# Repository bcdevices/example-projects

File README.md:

# Example Projects

A collection of KiCad hardware design projects, well mostly KiCad.
Confiential files should not be placed here!

## Structure

Each project lives in its own folder:

```
example-projects/
├── board-name-1/
│   ├── board-name-1.kicad_pro
│   ├── board-name-1.kicad_pcb
│   ├── board-name-1.kicad_sch
│   └── bom.csv
└── board-name-2/
    └── ...
```

## Files

| Extension | Description |
|---|---|
| `.kicad_pro` | KiCad project file |
| `.kicad_pcb` | PCB layout |
| `.kicad_sch` | Schematic |
| `.csv` | Bill of materials |

## Requirements

- [KiCad](https://www.kicad.org) 7.0 or later

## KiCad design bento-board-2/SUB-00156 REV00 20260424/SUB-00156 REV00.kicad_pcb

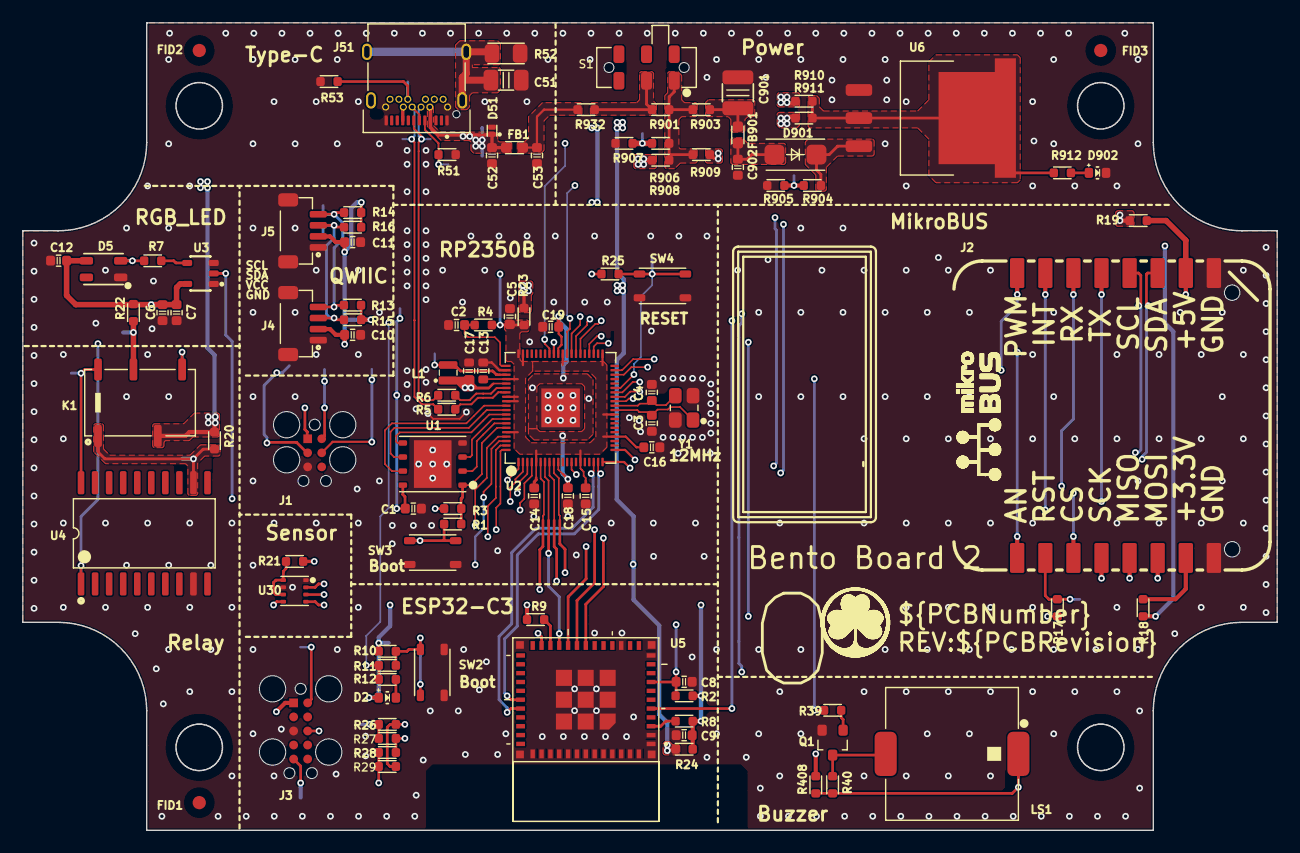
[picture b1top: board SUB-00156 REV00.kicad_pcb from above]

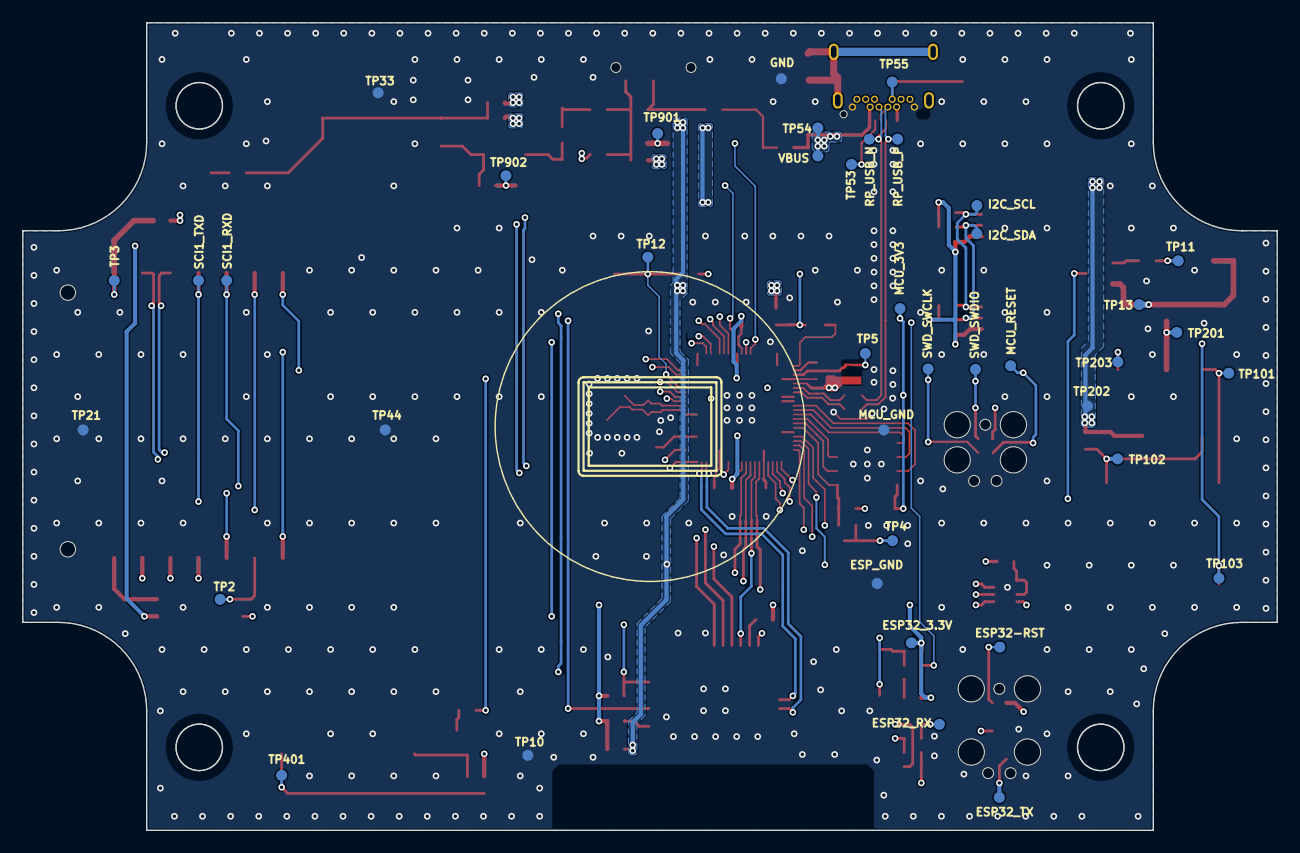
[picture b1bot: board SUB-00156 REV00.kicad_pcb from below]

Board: 4 copper layers, 113.4 x 73.0 mm, 153 parts (42 on the bottom side), 85 nets.

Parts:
BCD-Logo: BCD-Logo; LOGO_BCD_Product
Board ID label: 8*12mm; Laebl_12*8mm
C1, C7, C10, C11, C12, C14, C15, C16, C18, C19, C902: 0.1μF; CC0603-N
C2, C5, C9: 4.7μF; CC0603-N
C3, C4: 12pF; CC0603-N
C6, C8: 1μF; CC0603-N
C13, C17: 0.1μF; CC0603(1608)-N
C51: 100pF; CC1206-N
C52, C53: 100pF; CC0603-N
C901: 10μF; CC1210-N
D2, D902: LTST-C191KGKT; LED0603N-Green
D5: LTST-E683CEGBW; LTST-E683CEGBW-L
D51: SZESD7241N2T5G; 2-X2DFN (1x0.6)
D901: SK34A-LTP; SMA
ESP32-RST, ESP32_3.3V, ESP32_RX, ESP32_TX: TP-SM-39MILC
ESP_GND: TP-SM-39MILC
FB1, FB901: 26 Ohms@100 MHz; FB0603-N
FID1, FID2, FID3: Mark
GND: TP-SM-39MILC
I2C_SCL, I2C_SDA: TP-SM-39MILC
J1: TC2030-MCP-NL; TC2030-IDC
J2: MIKROE-4319
J3: TC2050-IDC
J4, J5: 16766
J51: 10159872-00011LF
K1: 1462042-8
L1: 3.3µH; IND-201610_SMD-2N
LS1: PKLCS1212E4001-R1
MCU_3V3: TP-SM-39MILC
MCU_GND: TP-SM-39MILC
MCU_RESET: TP-SM-39MILC
MH1, MH2, MH3, MH4: MountingHole; MH_.165NPT
OSHWA-Logo: OSHWA-Logo
PCB: CMP-000451 REV:00; PCB Part Number
PLT Tested label: 24*12mm; Laebl_24*12mm
Q1: MMBT3904-TP; SOT23
R1: 2K; RC0603-N
R2, R9, R10, R12, R13, R14, R15, R16: 10K; RC0603-N
R3, R25, R904: 100K; RC0603-N
R4, R5, R6: 27R; RC0603-N
R7: 1R; RC0603-N
R8, R11, R17, R18, R19, R20, R21, R22, R23, R24, R26, R27, R28, R29, R408, R901, R903, R908, R909, R910, R911, R932: 0R; RC0603-N
R39: 4.7K; RC0603-N
R40: 470R; RC0603-N
R51, R53: 5.1K; RC0603-N
R52: 267K; RC1206-N
R905: 150K; RC0603-N
R906: 470K; RC0603-N
R907: 68K; RC0603-N
R912: 1K; RC0603-N
RP_USB_N: TP-SM-39MILC
RP_USB_P: TP-SM-39MILC
S1: JS202011JAQN
SCI1_RXD, SCI1_TXD: TP-SM-39MILC
SW2, SW3, SW4: PTS810SJG250SMTR LFS
SWD_SWCLK: TP-SM-39MILC
SWD_SWDIO: TP-SM-39MILC
TP2, TP3, TP4, TP5, TP10, TP11, TP12, TP13, TP21, TP33, TP44, TP53, TP54, TP55, TP101, TP102, TP103, TP201, TP202, TP203, TP401, TP901, TP902: TP-SM-39MILC
U1: W25Q128JVPIQ; WSON127P6X5-8NP
U2: RP2350B; QFN040P10X10-80NPV
U3: SN74LVC1G125DBVR; SOT23-5
U4: ULN2803CDWR; SOIC127P10.3X2.65-20N
U5: ESP32-C3-MINI-1-N4
U6: LM1086ISX-3.3/NOPB; TO-263
U30: BME280; LGA065P2.5X2.5-8N
VBUS: TP-SM-39MILC
Y1: 12 MHz; OSC3.2X2.5-4N

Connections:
+3.3V: R21.1, R23.1, R24.1, R408.1, R911.2
+5V: K1.3, R20.2, R908.2, TP202.1
ADC0: R904.2, R905.1, TP902.1, U2.49
ADC1: J2.1, U2.52
ADC2: R906.2, R907.1, TP901.1, U2.53
AUDIO_EN: Q1.1, R39.2
AVDD: C2.1, R4.1, U2.61
BOOT: R10.1, R11.1, SW2.3, SW2.4, U5.23
BUZZER_VSYS: LS1.1, R40.1, R408.2, TP401.1
BootSet: R1.2, SW3.1, SW3.2, TP4.1
C3_SPI.MISO: U2.77, U5.19
C3_SPI.MOSI: U2.80, U5.18
C3_SPI.SCK: U2.79, U5.20
CC1: J51.A5, R51.1, TP53.1
CC2: J51.B5, R53.1, TP55.1
COIL_N: K1.8, TP101.1, U4.20
ESP32-RST: C8.1, ESP32-RST.1, J3.10, R2.2, U2.48, U5.8
ESP32_3.3V: C9.1, D2.1, ESP32_3.3V.1, J3.1, R2.1, R8.2, R9.2, R10.2, R24.2
ESP32_RX: ESP32_RX.1, J3.8, R26.1, R27.1
ESP32_RXD0: R26.2, R29.2, U2.19, U5.30
ESP32_TX: ESP32_TX.1, J3.5, R28.1, R29.1
ESP32_TXD0: R27.2, R28.2, U2.18, U5.31
GND: C1.2, C2.2, C3.2, C4.2, C5.2, C6.2, C7.2, C8.2, C9.2, C10.2, C11.2, C12.2, C13.2, C14.2, C15.2, C16.2, C17.2, C18.2, C19.2, C51.2, C52.2, C53.2, C901.2, C902.2, D5.1, D51.2, D902.2, ESP_GND.1, GND.1, J1.5, J2.8, J2.9, J3.3, J4.1, J4.SH1, J4.SH2, J5.1, J5.SH1, J5.SH2, J51.A1, J51.A12, J51.B1, J51.B12, MCU_GND.1, Q1.2, R51.2, R52.2, R53.2, R905.2, R907.2, SW2.1, SW2.2, SW3.3, SW3.4, SW4.1, SW4.2, TP10.1, TP21.1, TP33.1, TP44.1, U1.4, U1.9, U2.62, U2.81, U3.1, U3.3, U4.9, U5.1, U5.2, U5.11, U5.14, U5.36, U5.37, U5.38, U5.39, U5.40, U5.41, U5.42, U5.43, U5.44, U5.45, U5.46, U5.47, U5.48, U5.49_1, U5.49_2, U5.49_3, U5.49_4, U5.49_5, U5.49_6, U5.49_7, U5.49_8, U5.49_9, U5.50, U5.51, U5.52, U5.53, U6.1, U30.1, U30.7, Y1.2, Y1.4
IO_STRAP: R9.1, U5.22
K_NC: K1.7, R22.1, TP201.1
K_NO: K1.5, TP203.1
LED_DIN: D5.2, R7.2, TP11.1
LED_OUT: R7.1, U3.4
MCU_3V3: C1.1, C5.1, C13.1, C14.1, C15.1, C16.1, J1.1, MCU_3V3.1, R3.1, R4.2, R23.2, R25.2, U1.8, U2.5, U2.15, U2.24, U2.29, U2.41, U2.50, U2.59, U2.60, U2.64, U2.68, U2.69, U2.76
MCU_RESET: J1.3, MCU_RESET.1, R25.1, SW4.3, SW4.4, TP12.1, U2.35
MIKRO_3V3: J2.7, R18.2
MIKRO_5V: J2.10, R19.1, TP3.1
MIKRO_5V_IN: R19.2, R909.2
NetD2_2: D2.2, R12.2
NetD902_1: D902.1, R912.2
NetLS1_2: LS1.2, Q1.3, R40.2
NetR8_1: R8.1, U5.3
NetR901_1: R901.1, R932.2, S1.2
OUT_3V3: C10.1, C11.1, J4.2, J5.2, R13.1, R14.1, R15.1, R16.1, R18.1, R910.2
QSPI_SCLK: U1.6, U2.71
QSPI_SD0: U1.5, U2.72
QSPI_SD1: U1.2, U2.74
QSPI_SD2: U1.3, U2.73
QSPI_SD3: U1.7, U2.70
QSPI_SS0: R1.1, R3.2, U1.1, U2.75
RGB_5V: C6.1, C7.1, C12.1, D5.4, R22.2, TP13.1, U3.5
RP_PWM0: R39.1, U2.38
RP_PWM1: J2.16, U2.39
RP_S0: R17.1, U2.43
RP_S1: TP103.1, U2.44, U4.1
RP_S2: U2.13, U3.2
RP_S3: R11.2, R12.1, U2.46
RP_S4: U2.47, U5.5
RP_USB_N: J51.A7, J51.B7, R6.1, RP_USB_N.1
RP_USB_P: J51.A6, J51.B6, R5.1, RP_USB_P.1
RSPI0_SSL0: U2.78, U30.2
RTS: J2.2, R17.2, TP2.1
SCI1_CTS: J2.15, U2.4
SCI1_RTS: J2.3, U2.3
SCI1_RXD: J2.13, SCI1_TXD.1, U2.2
SCI1_TXD: J2.14, SCI1_RXD.1, U2.1
SENS_I2C.SCL: I2C_SCL.1, J2.12, J4.4, J5.4, R13.2, R14.2, U2.21
SENS_I2C.SDA: I2C_SDA.1, J2.11, J4.3, J5.3, R15.2, R16.2, U2.20
SENS_SPI.MISO: J2.5, U2.6, U30.5
SENS_SPI.MOSI: J2.6, U2.9, U30.3
SENS_SPI.SCK: J2.4, U2.8, U30.4
SHIELD: C51.1, J51.SH, R52.1
SPIS_SS: U2.7, U5.21
SWD_SWCLK: J1.4, SWD_SWCLK.1, U2.33
SWD_SWDIO: J1.2, SWD_SWDIO.1, U2.34
USB_N: R6.2, U2.66
USB_P: R5.2, U2.67
USB_VBUS: C53.1, FB1.2, R932.1
VBUS: C52.1, D51.1, FB1.1, J51.A4, J51.A9, J51.B4, J51.B9, TP54.1, VBUS.1
VBUS4V65: D901.2, R904.1, U6.3
VBUS5V: C902.1, D901.1, FB901.2
VBUSIN: C901.1, FB901.1, R903.2
VBUS_5V: R901.2, R903.1, R906.1, R908.1, R909.1, S1.1
VREG_3V3: R910.1, R911.1, R912.1, U6.2, U6.4
VREG_FB: C17.1, C18.1, C19.1, L1.1, U2.10, U2.32, U2.51, U2.65
VREG_LX: L1.2, TP5.1, U2.63
VSYS_3V3: R21.2, U30.6, U30.8
VSYS_5V: K1.1, R20.1, TP102.1, U4.12
XIN: C3.1, U2.30, Y1.1
XOUT: C4.1, U2.31, Y1.3

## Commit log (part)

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2026-04-15 Remove incorrectly nested repos
2026-04-15 Remove .DS_Store
2026-04-15 Add initial example projects
2026-04-16 emphasized not to put confidential stuff here.
    Clarified project description and added confidentiality note.
2026-04-16 Add example project files
2026-04-24 Add Bento Board 2 REV00 KiCad source files
2026-04-24 Flatten directory structure
2026-05-07 Add bento blinky flashing test plans.
2026-05-07 Remove .DS_Stores
2026-05-07 Add blinky Zephyr programs for bento1 + 2.
    Note that currently the bento2 example is the same as bento1
2026-05-07 Blinky.hex is the filename now
2026-05-07 added svg files for pcb and schem
2026-05-08 Update example test plans
